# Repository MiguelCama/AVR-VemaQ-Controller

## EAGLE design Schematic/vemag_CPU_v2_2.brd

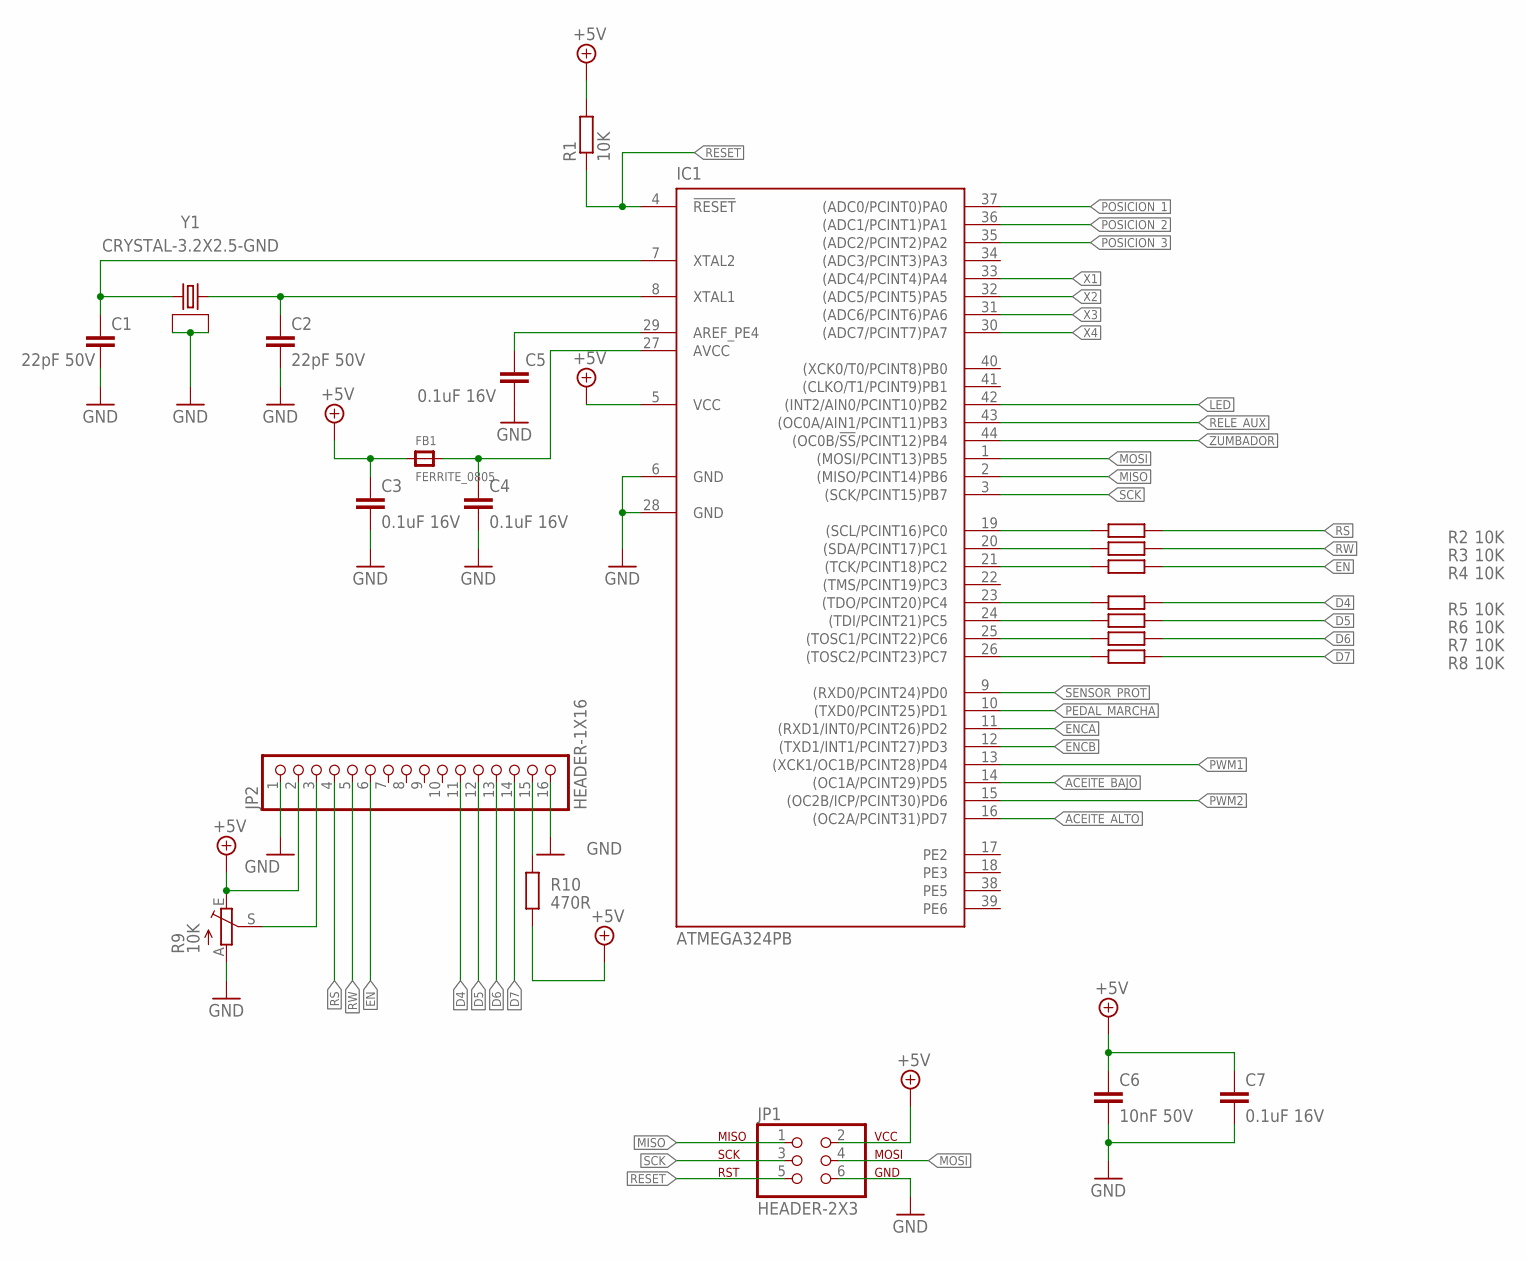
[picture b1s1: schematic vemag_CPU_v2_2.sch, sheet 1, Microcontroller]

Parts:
C1, C2: 22pF 50V; C0603
C3, C4, C5, C7: 0.1uF 16V; C0603
C6: 10nF 50V; C0603
FB1: FERRITE_0805; _0805
IC1: ATMEGA324PB; TQFP44
JP1: HEADER-2X3; ISP_AVR_6P
JP2: HEADER-1X16; 1X16
R1, R2, R3, R4, R5, R6, R7, R8: 10K; R0805
R9: 10K; CA6V
R10: 470R; R0805
Y1: CRYSTAL-3.2X2.5-GND; CRYSTAL-SMD-3.2X2.5MM

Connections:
+5V: C3.1, C6.1, C7.1, FB1.1, IC1.5 (VCC), JP1.2, JP2.2, R1.2, R9.E, R10.1; also elsewhere on the board
ACEITE_ALTO: IC1.16 ((OC2A/PCINT31)PD7); also elsewhere on the board
ACEITE_BAJO: IC1.14 ((OC1A/PCINT29)PD5); also elsewhere on the board
D4: JP2.11, R5.1
D5: JP2.12, R6.1
D6: JP2.13, R7.1
D7: JP2.14, R8.1
EN: JP2.6, R4.1
ENCA: IC1.11 ((RXD1/INT0/PCINT26)PD2); also elsewhere on the board
ENCB: IC1.12 ((TXD1/INT1/PCINT27)PD3); also elsewhere on the board
GND: C1.2, C2.2, C3.2, C4.2, C5.2, C6.2, C7.2, IC1.6 (GND), IC1.28 (GND), JP1.6, JP2.1, JP2.16, R9.A, Y1.2 (GND), Y1.4 (GND); also elsewhere on the board
LED: IC1.42 ((INT2/AIN0/PCINT10)PB2)
MISO: IC1.2 ((MISO/PCINT14)PB6), JP1.1
MOSI: IC1.1 ((MOSI/PCINT13)PB5), JP1.4
unnamed: C1.1, IC1.7 (XTAL2), Y1.1 (2)
unnamed: C2.1, IC1.8 (XTAL1), Y1.3 (1)
unnamed: C5.1, IC1.29 (AREF_PE4)
unnamed: JP2.3, R9.S
unnamed: C4.1, FB1.2, IC1.27 (AVCC)
unnamed: IC1.26 ((TOSC2/PCINT23)PC7), R8.2
unnamed: IC1.25 ((TOSC1/PCINT22)PC6), R7.2
unnamed: IC1.24 ((TDI/PCINT21)PC5), R6.2
unnamed: IC1.23 ((TDO/PCINT20)PC4), R5.2
unnamed: IC1.21 ((TCK/PCINT18)PC2), R4.2
unnamed: IC1.20 ((SDA/PCINT17)PC1), R3.2
unnamed: IC1.19 ((SCL/PCINT16)PC0), R2.2
unnamed: JP2.15, R10.2
PE2: IC1.17 (PE2)
PE3: IC1.18 (PE3)
PE5: IC1.38 (PE5)
PE6: IC1.39 (PE6)
PEDAL_MARCHA: IC1.10 ((TXD0/PCINT25)PD1); also elsewhere on the board
POSICION_1: IC1.37 ((ADC0/PCINT0)PA0); also elsewhere on the board
POSICION_2: IC1.36 ((ADC1/PCINT1)PA1); also elsewhere on the board
POSICION_3: IC1.35 ((ADC2/PCINT2)PA2); also elsewhere on the board
PWM1: IC1.13 ((XCK1/OC1B/PCINT28)PD4); also elsewhere on the board
PWM2: IC1.15 ((OC2B/ICP/PCINT30)PD6); also elsewhere on the board
RELE_AUX: IC1.43 ((OC0A/AIN1/PCINT11)PB3); also elsewhere on the board
RESET: IC1.4 (!RESET), JP1.5, R1.1
RS: JP2.4, R2.1
RW: JP2.5, R3.1
SCK: IC1.3 ((SCK/PCINT15)PB7), JP1.3
SENSOR_PROT: IC1.9 ((RXD0/PCINT24)PD0); also elsewhere on the board
X1: IC1.33 ((ADC4/PCINT4)PA4); also elsewhere on the board
X2: IC1.32 ((ADC5/PCINT5)PA5); also elsewhere on the board
X3: IC1.31 ((ADC6/PCINT6)PA6); also elsewhere on the board
X4: IC1.30 ((ADC7/PCINT7)PA7); also elsewhere on the board
ZUMBADOR: IC1.44 ((OC0B/!SS!/PCINT12)PB4); also elsewhere on the board

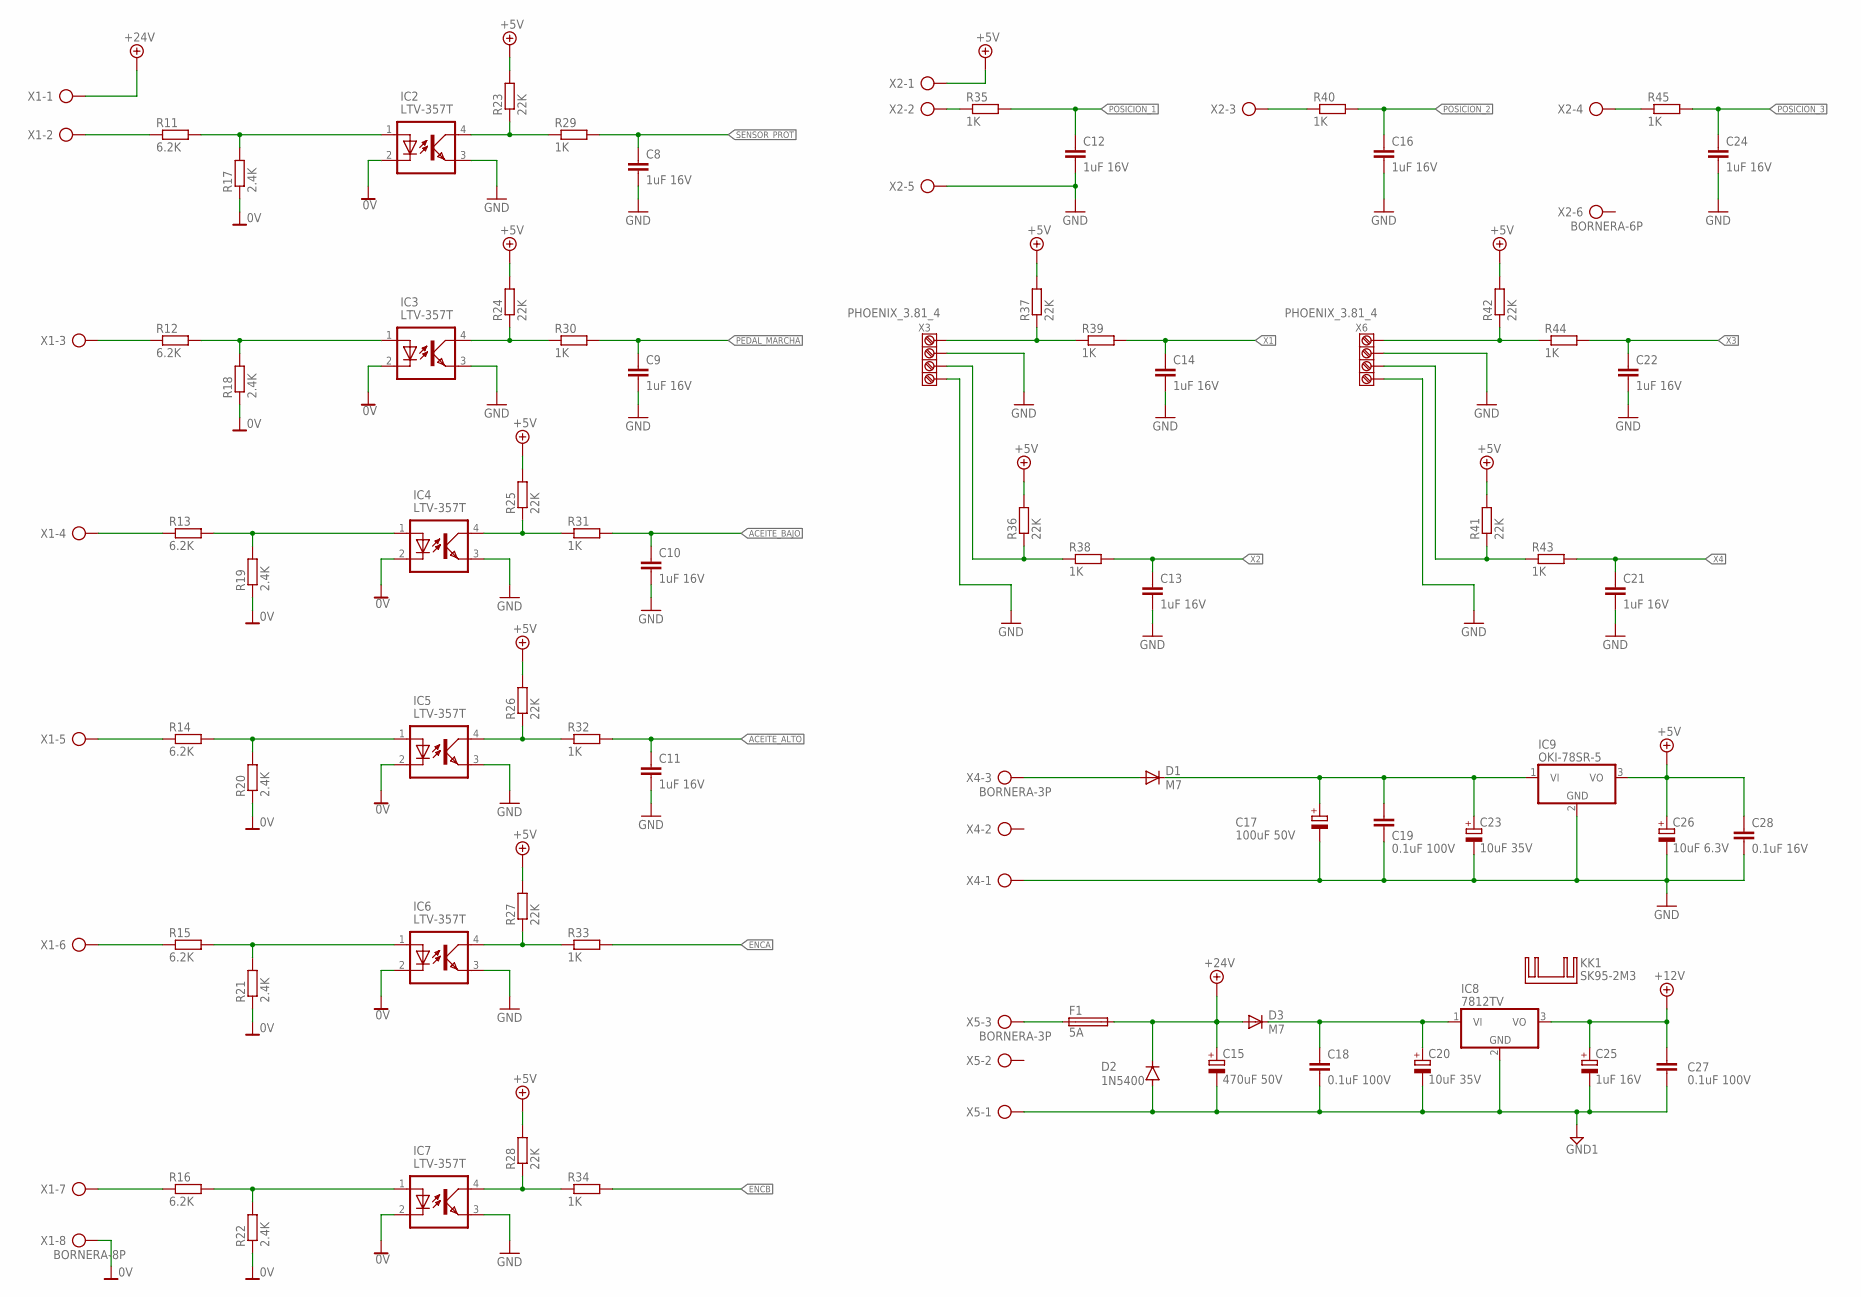
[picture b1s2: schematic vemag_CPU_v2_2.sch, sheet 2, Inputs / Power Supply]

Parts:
C8, C9, C10, C11, C12, C13, C14, C16, C21, C22, C24: 1uF 16V; C0805
C15: 470uF 50V; EB20D
C17: 100uF 50V; E5-10,5
C18, C19, C27: 0.1uF 100V; C050-035X075
C20, C23: 10uF 35V; SMC_D
C25: 1uF 16V; SMC_C
C26: 10uF 6.3V; SMC_C
C28: 0.1uF 16V; C0603
D1, D3: M7; DIODE_DO-214AC
D2: 1N5400; DO201-15
F1: 5A; TR5
IC2, IC3, IC4, IC5, IC6, IC7: LTV-357T
IC8: 7812TV; TO220V
IC9: OKI-78SR-5; TO220V-OKI-ISO
KK1: SK95-2M3
R11, R12, R13, R14, R15, R16: 6.2K; R1206
R17, R18, R19, R20, R21, R22: 2.4K; R1206
R23, R24, R25, R26, R27, R28, R36, R37, R41, R42: 22K; R0805
R29, R30, R31, R32, R33, R34, R35, R38, R39, R40, R43, R44, R45: 1K; R0805
X1: BORNERA-8P; AK500/8
X2: BORNERA-6P; AK500/6
X3, X6: PHOENIX_3.81_4; 3.81-4
X4, X5: BORNERA-3P; AK500/3

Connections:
0V: IC2.2 (CATHODE), IC3.2 (CATHODE), IC4.2 (CATHODE), IC5.2 (CATHODE), IC6.2 (CATHODE), IC7.2 (CATHODE), R17.1, R18.1, R19.1, R20.1, R21.1, R22.1, X1.8
+5V: C26.+, C28.1, IC9.3 (VO), R23.2, R24.2, R25.2, R26.2, R27.2, R28.2, R36.2, R37.2, R41.2, R42.2, X2.1; also elsewhere on the board
+12V: C25.+, C27.1, IC8.3 (VO); also elsewhere on the board
+24V: C15.+, D2.C, D3.A, F1.2, X1.1; also elsewhere on the board
ACEITE_ALTO: C11.1, R32.2; also elsewhere on the board
ACEITE_BAJO: C10.1, R31.2; also elsewhere on the board
ENCA: R33.2; also elsewhere on the board
ENCB: R34.2; also elsewhere on the board
GND: C8.2, C9.2, C10.2, C11.2, C12.2, C13.2, C14.2, C16.2, C17.-, C19.2, C21.2, C22.2, C23.-, C24.2, C26.-, C28.2, IC2.3 (EM), IC3.3 (EM), IC4.3 (EM), IC5.3 (EM), IC6.3 (EM), IC7.3 (EM), IC9.2 (GND), X2.5, X3.2, X3.4, X4.1, X6.2, X6.4; also elsewhere on the board
GND1: C15.-, C18.2, C20.-, C25.-, C27.2, D2.A, IC8.2 (GND), X5.1; also elsewhere on the board
unnamed: D1.A, X4.3
unnamed: IC2.1 (ANODE), R11.2, R17.2
unnamed: IC2.4 (COL), R23.1, R29.1
unnamed: R35.1, X2.2
unnamed: IC3.1 (ANODE), R12.2, R18.2
unnamed: C18.1, C20.+, D3.C, IC8.1 (VI)
unnamed: IC3.4 (COL), R24.1, R30.1
unnamed: IC4.1 (ANODE), R13.2, R19.2
unnamed: IC4.4 (COL), R25.1, R31.1
unnamed: IC5.1 (ANODE), R14.2, R20.2
unnamed: IC5.4 (COL), R26.1, R32.1
unnamed: IC6.1 (ANODE), R15.2, R21.2
unnamed: IC6.4 (COL), R27.1, R33.1
unnamed: IC7.1 (ANODE), R16.2, R22.2
unnamed: IC7.4 (COL), R28.1, R34.1
unnamed: R16.1, X1.7
unnamed: R15.1, X1.6
unnamed: R14.1, X1.5
unnamed: R13.1, X1.4
unnamed: R12.1, X1.3
unnamed: R11.1, X1.2
unnamed: F1.1, X5.3
unnamed: C17.+, C19.1, C23.+, D1.C, IC9.1 (VI)
unnamed: R40.1, X2.3
unnamed: R45.1, X2.4
unnamed: R37.1, R39.1, X3.1
unnamed: R36.1, R38.1, X3.3
unnamed: R42.1, R44.1, X6.1
unnamed: R41.1, R43.1, X6.3
PEDAL_MARCHA: C9.1, R30.2; also elsewhere on the board
POSICION_1: C12.1, R35.2; also elsewhere on the board
POSICION_2: C16.1, R40.2; also elsewhere on the board
POSICION_3: C24.1, R45.2; also elsewhere on the board
SENSOR_PROT: C8.1, R29.2; also elsewhere on the board
X1: C14.1, R39.2; also elsewhere on the board
X2: C13.1, R38.2; also elsewhere on the board
X3: C22.1, R44.2; also elsewhere on the board
X4: C21.1, R43.2; also elsewhere on the board

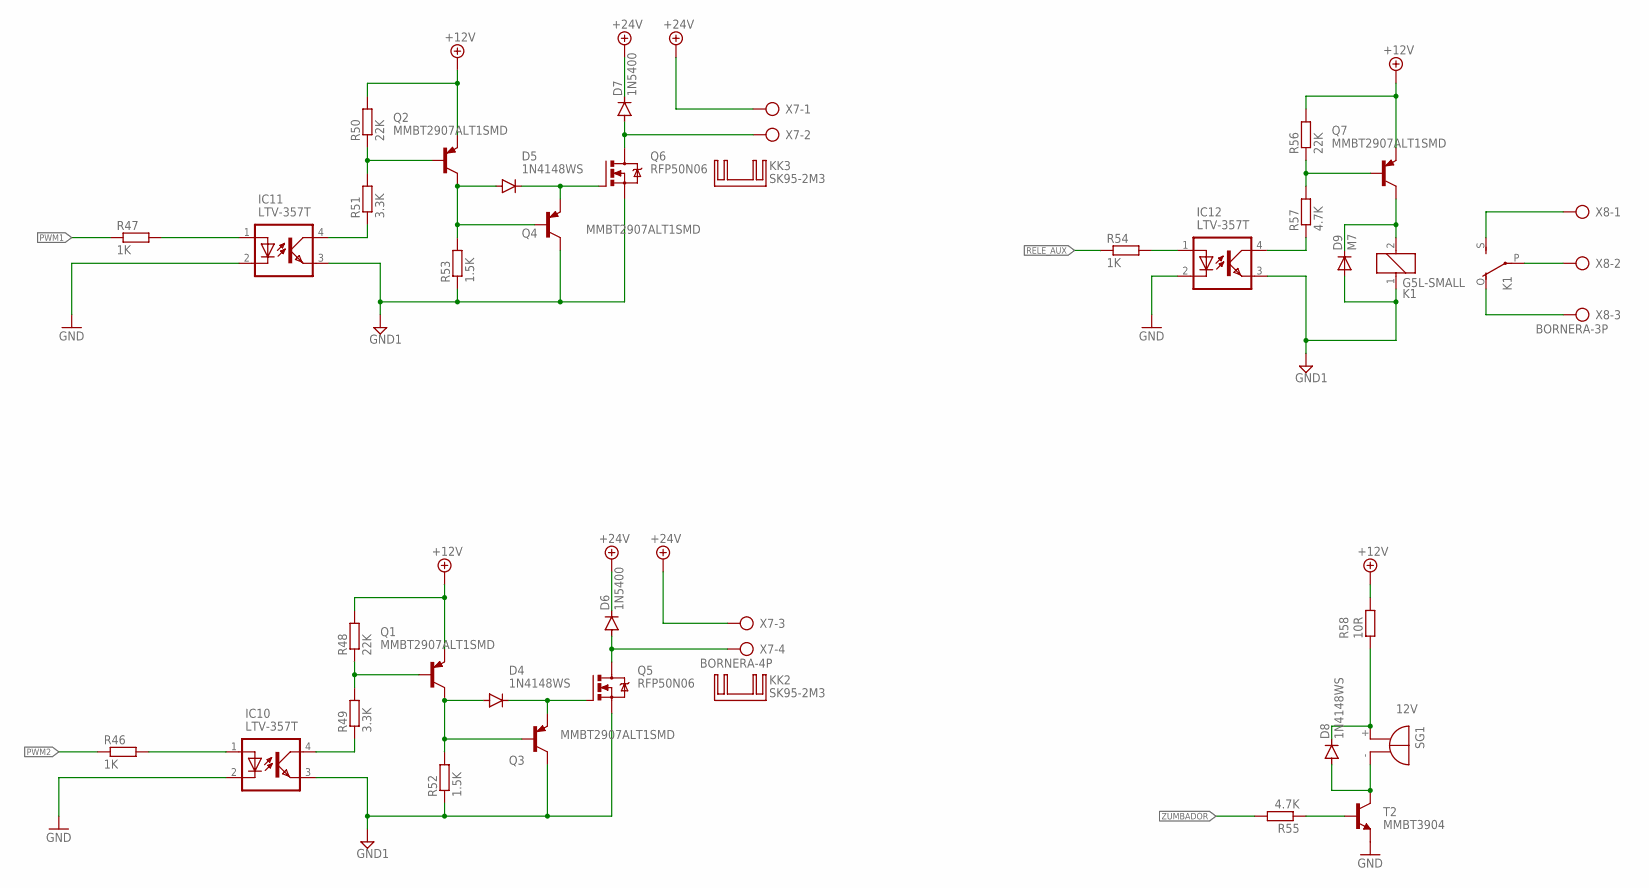
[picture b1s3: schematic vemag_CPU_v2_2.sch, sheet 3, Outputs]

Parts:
D4, D5, D8: 1N4148WS; DIODE_SOD323-W
D6, D7: 1N5400; DO201-15
D9: M7; DIODE_DO-214AC
IC10, IC11, IC12: LTV-357T
K1: G5L-SMALL; G5LE-SMALL
KK2, KK3: SK95-2M3
Q1, Q2, Q3, Q4, Q7: MMBT2907ALT1SMD; SOT23-BEC
Q5, Q6: RFP50N06; TO220BV
R46, R47, R54: 1K; R0805
R48, R50, R56: 22K; R0805
R49, R51: 3.3K; R0805
R52, R53: 1.5K; R1206
R55, R57: 4.7K; R0805
R58: 10R; R0805
SG1: 12V; F/TMB
T2: MMBT3904; SOT23-BEC
X7: BORNERA-4P; AK500/4
X8: BORNERA-3P; AK500/3

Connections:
+12V: Q1.E, Q2.E, Q7.E, R48.2, R50.2, R56.2, R58.1; also elsewhere on the board
+24V: D6.C, D7.C, X7.1, X7.3; also elsewhere on the board
GND: IC10.2 (CATHODE), IC11.2 (CATHODE), IC12.2 (CATHODE), T2.E; also elsewhere on the board
GND1: D9.A, IC10.3 (EM), IC11.3 (EM), IC12.3 (EM), K1.1, Q3.C, Q4.C, Q5.S, Q6.S, R52.1, R53.1; also elsewhere on the board
unnamed: IC11.1 (ANODE), R47.2
unnamed: D8.C, R58.2, SG1.+
unnamed: D5.A, Q2.C, Q4.B, R53.2
unnamed: IC11.4 (COL), R51.1
unnamed: Q2.B, R50.1, R51.2
unnamed: IC10.1 (ANODE), R46.2
unnamed: D5.C, Q4.E, Q6.G
unnamed: D7.A, Q6.D, X7.2
unnamed: K1.S, X8.1
unnamed: K1.P, X8.2
unnamed: IC10.4 (COL), R49.1
unnamed: Q1.B, R48.1, R49.2
unnamed: D4.A, Q1.C, Q3.B, R52.2
unnamed: D4.C, Q3.E, Q5.G
unnamed: D6.A, Q5.D, X7.4
unnamed: IC12.1 (ANODE), R54.2
unnamed: IC12.4 (COL), R57.1
unnamed: Q7.B, R56.1, R57.2
unnamed: D9.C, K1.2, Q7.C
unnamed: K1.O, X8.3
unnamed: R55.1, T2.B
unnamed: D8.A, SG1.-, T2.C
PWM1: R47.1; also elsewhere on the board
PWM2: R46.1; also elsewhere on the board
RELE_AUX: R54.1; also elsewhere on the board
ZUMBADOR: R55.2; also elsewhere on the board

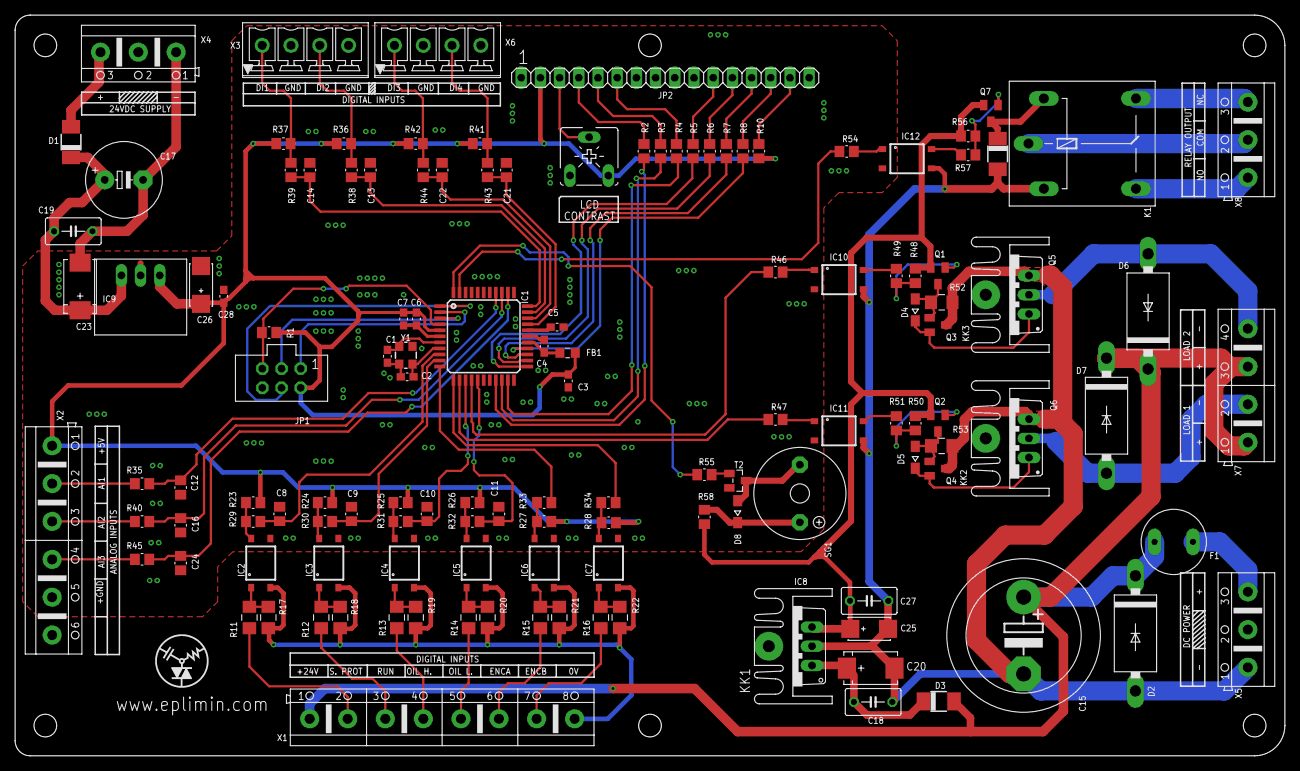
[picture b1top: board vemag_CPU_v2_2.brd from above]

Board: 2 copper layers, 168.0 x 98.0 mm, 133 parts (0 on the bottom side), 98 nets.

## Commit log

2024-03-04 First Version
